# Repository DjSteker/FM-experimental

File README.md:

# FM-experimental
Modelo de emisor de frecuencia modulada

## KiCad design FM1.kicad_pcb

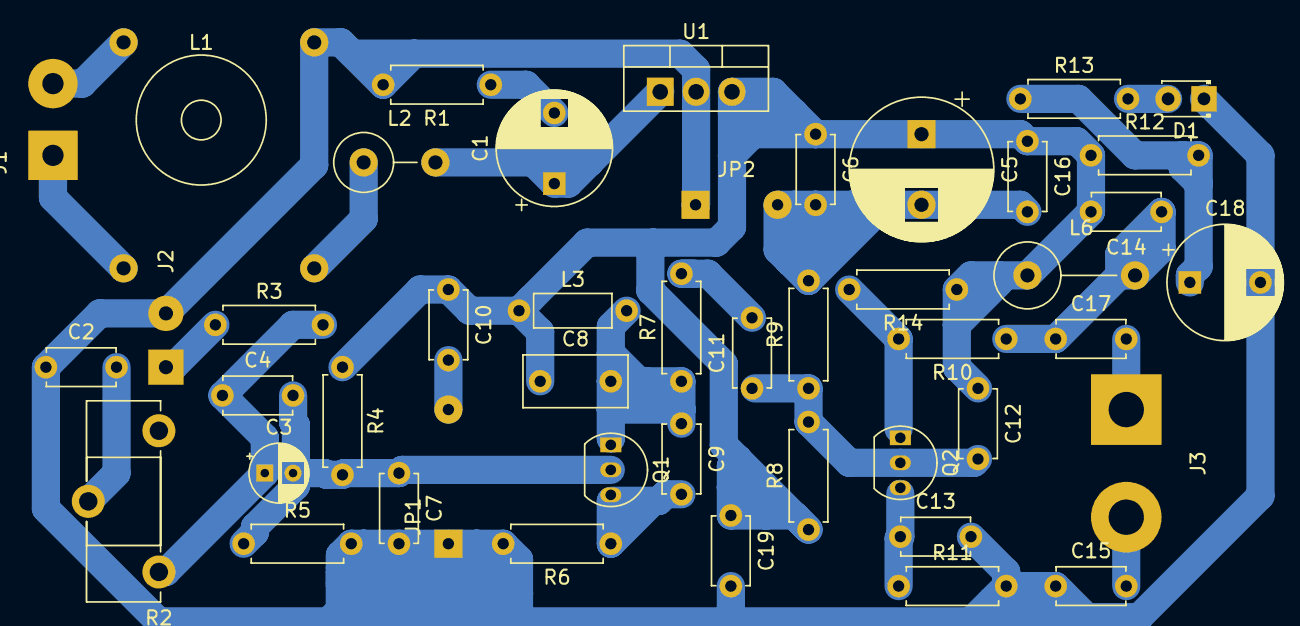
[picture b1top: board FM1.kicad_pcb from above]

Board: 2 copper layers, 46 parts (0 on the bottom side), 23 nets.

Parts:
C1, C18: CP; CP_Radial_D8.0mm_P5.00mm
C2, C4, C6, C7, C9, C10, C11, C12, C13, C14, C15, C16, C17, C19: C; C_Disc_D4.7mm_W2.5mm_P5.00mm
C3: CP; CP_Radial_D4.0mm_P2.00mm
C5: CP; CP_Radial_D10.0mm_P5.00mm
C8: C_Variable; C_Rect_L7.2mm_W3.5mm_P5.00mm_FKS2_FKP2_MKS2_MKP2
D1: LED; LED_D1.8mm_W3.3mm_H2.4mm
J1: Conn_01x02; SolderWirePad_1x02_P5.08mm_Drill1.5mm
J2: Conn_01x02; SolderWirePad_1x02_P3.81mm_Drill1mm
J3: Conn_01x02; SolderWirePad_1x02_P7.62mm_Drill2.5mm
JP1: Jumper; SolderWirePad_1x02_P3.81mm_Drill0.8mm
JP2: Jumper_NC_Small; SolderWirePad_1x02_P3.81mm_Drill0.8mm
L1: L_Core_Ferrite_Coupled; Transformer_Toroid_Horizontal_D9.0mm_Amidon-T30
L2: L_Core_Ferrite; L_Axial_L9.5mm_D4.0mm_P5.08mm_Vertical_Fastron_SMCC
L3: L; L_Axial_L5.3mm_D2.2mm_P7.62mm_Horizontal_Vishay_IM-1
L6: L_Core_Iron; L_Axial_L14.0mm_D4.5mm_P7.62mm_Vertical_Fastron_LACC
Q1, Q2: BC547; TO-92_Inline
R1, R3, R4, R5, R6, R7, R8, R9, R10, R11, R12, R13, R14: R; R_Axial_DIN0207_L6.3mm_D2.5mm_P7.62mm_Horizontal
R2: R_Variable_US; Potentiometer_ACP_CA14-H5_Horizontal
U1: LM7808_TO220; TO-220-3_Vertical

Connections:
GNDD: C2.1, C5.2, C6.2, C7.2, C13.2, C15.1, C16.2, C18.2, C19.2, D1.1, J2.2, JP1.1, JP2.1, JP2.2, L1.4, R1.2, R5.2, R6.2, R9.2, R11.2, U1.2
unnamed: C1.1, L2.2, U1.1
unnamed: C1.2, R1.1
unnamed: C2.2, R2.2
unnamed: C3.1, C4.1, R2.1, R3.2
unnamed: C3.2, C4.2, C7.1, Q1.2, R4.2, R5.1
unnamed: C8.2, C9.1, L3.2, Q1.1, R7.1
unnamed: C9.2, Q1.3, R6.1
unnamed: C5.1, C6.1, C8.1, C10.1, C12.1, C14.2, C16.1, C19.1, L3.1, L6.1, R4.1, R8.1, R12.1, R14.1, U1.3
unnamed: C10.2, JP1.2
unnamed: C11.1, C12.2, Q2.2, R8.2, R9.1
unnamed: C11.2, R7.2
unnamed: C13.1, Q2.3, R11.1
unnamed: C14.1, C17.1, L6.2, R10.1
unnamed: C15.2, J3.2
unnamed: C17.2, J3.1
unnamed: C18.1, R12.2, R13.1
unnamed: D1.2, R13.2
unnamed: J1.1, L1.1
unnamed: J1.2, L1.3
unnamed: J2.1, R3.1
unnamed: L1.2, L2.1
unnamed: Q2.1, R10.2, R14.2
